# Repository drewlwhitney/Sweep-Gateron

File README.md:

[Head Repository](https://github.com/davidphilipbarr/Sweep)

# Sweep Gateron

<sub>Wireless Ferris Sweep with Gateron KS-33 switches and [Nyphy COAST Dawn](https://nuphy.com/collections/keycaps/products/coast-dawn-nsa?_pos=16&_fid=9b29c1ae1&_ss=c) keycaps</sub>

A modified Ferris Sweep for [Gateron KS-33 switches](https://www.gateron.co/products/gateron-low-profile-mechanical-switch-set) ([hotswap sockets](https://www.gateron.com/products/gateron-low-profile-switch-hot-swap-pcb-socket?VariantsId=10234) required).

## Variants
- [Basic](./Sweep-Gateron/) - MX spacing, based on the [Sweep High](https://github.com/davidphilipbarr/Sweep/tree/main/Sweep%20High).
- [JST](./Sweep-Gateron/jst/) - Same as the basic version, but the TRS jack is replaced with a 2-pin JST connector for the battery in wireless builds (and the reset button is moved). **Wireless only**.
- [JST-TRS](./Sweep-Gateron/jst-trs/) - Same as the basic version, but adds a 2-pin JST connector (for a battery) on top of the TRS jack. Can be used for wired *or* wireless builds.

All variants support a [switch plate](./Sweep-Gateron/switch-plate/) and [bottom plate](./Sweep-Gateron/bottom-plate/).

## Components
Unless otherwise stated, this Sweep uses the same components as the base Sweep.

- The JST connector for the JST version is from [typeractive](https://typeractive.xyz/products/battery-jack).

- This board *does not* support a tenting puck, but great alternatives are tenting kickstands (from [typeractive](https://typeractive.xyz/products/battery-jack))
 or MagSafe tenting stands (from [Keebio](https://keeb.io/products/magnetic-magsafe-tenting-stand-kit-for-split-keyboard-r2)).

## Gallery
### Front

### Back

## Notes
- If you edit this board, be aware that the schematic files are affected by [#75](https://github.com/davidphilipbarr/Sweep/issues/75). The PCB files are correct according to the software pinout, however, and will be manufactured correctly.

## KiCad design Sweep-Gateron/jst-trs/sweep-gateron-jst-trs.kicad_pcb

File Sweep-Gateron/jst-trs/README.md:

# Sweep Gateron (JST-TRS)
Adds a 2-pin JST connector in the same position as the TRS connector. This can be used for wired or wireless builds. The JST connector can be purchased [here](https://typeractive.xyz/products/battery-jack).

## Build Instructions
See the [Sweep High](https://github.com/davidphilipbarr/Sweep/tree/main/Sweep%20Bling%20MX) folder for PCB manufacturing instructions.

### Gerber Files
Can be found [here](./gerber_to_order/).

### Switch Plate and Bottom Plate
Can be found [here](../switch-plate/) and [here](../bottom-plate/), respectively.

## Added Footprints
- [2-pin JST Connector](https://app.ultralibrarian.com/details/fbd6f894-563c-11ea-8c00-0ad2c9526b44/JST/S2B-PH-K-S-LF-SN-?exports=42&open=exports)

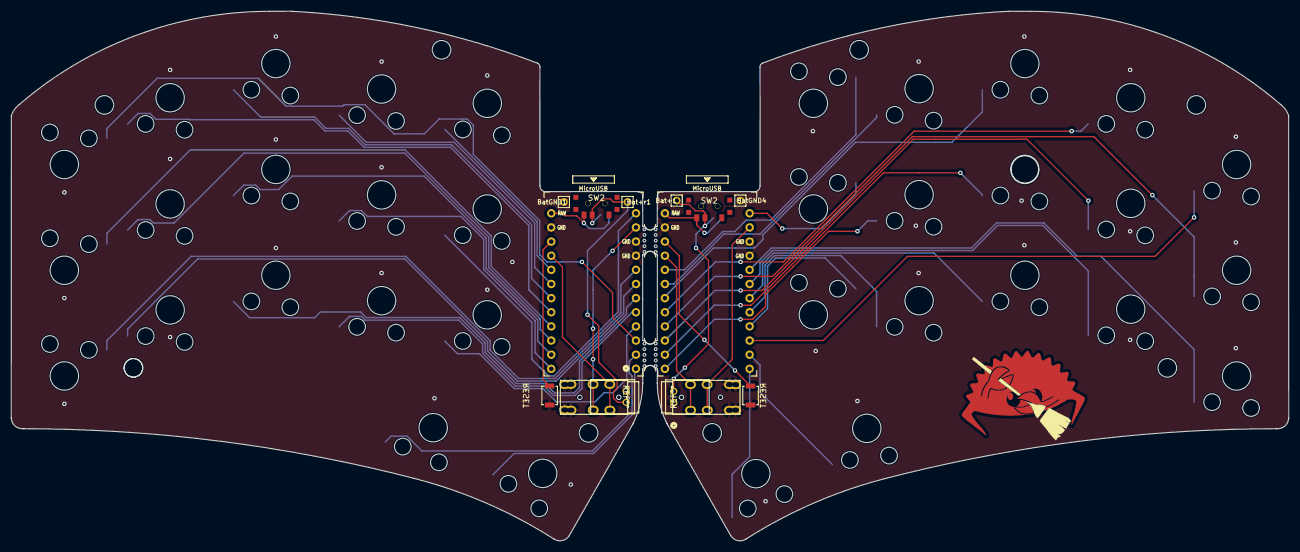
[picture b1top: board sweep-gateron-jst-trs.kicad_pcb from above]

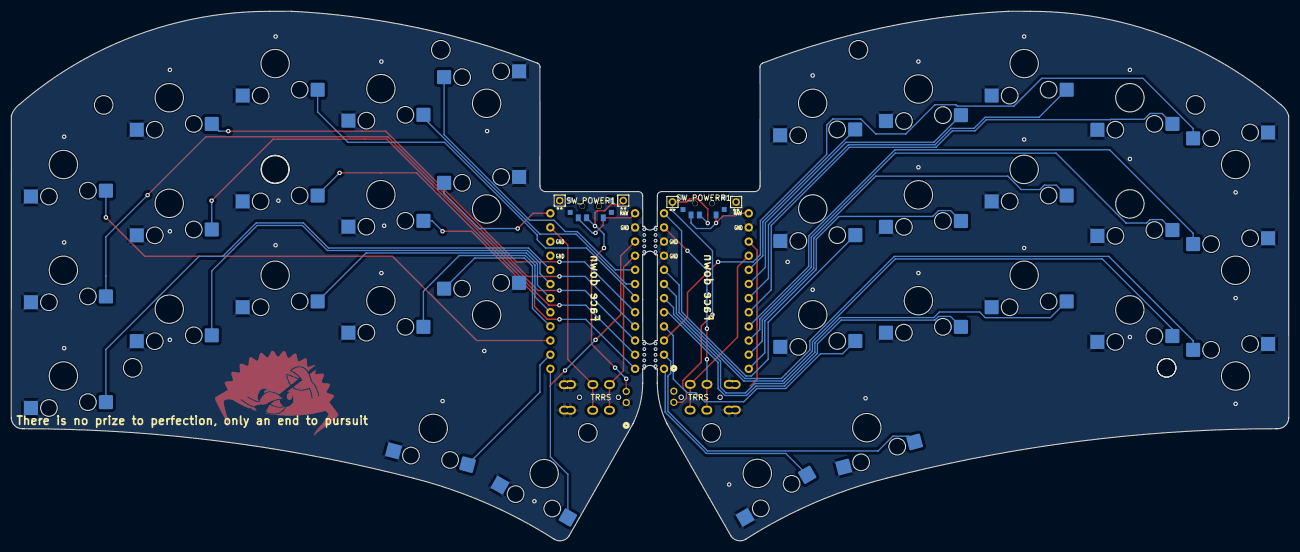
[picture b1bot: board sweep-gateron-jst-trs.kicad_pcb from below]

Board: 2 copper layers, 229.5 x 95.2 mm, 58 parts (40 on the bottom side), 43 nets.

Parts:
Bat+1: MountingHole_Pad; 1pin_conn
Bat+r1: MountingHole_Pad; 1pin_conn
BatGND1, BatGND4: MountingHole_Pad; 1pin_conn
J1, J2: AudioJack4dpb; TRRS-PJ-DPB2
Mounting 01, Mounting 01#2, Mounting 02, Mounting 02#2, Mounting 03, Mounting 03#2, Mounting 04, Mounting 04#2: MountingHole_3.35mm
RSW1, RSW2: SW_Push; SW_SPST_B3U-1000P
SW2, SW2#2: SW_SPDT; SPDT_C128955r
SW2#3, SW2_r1, SW3, SW3_r1, SW4, SW4_r1, SW5, SW5_r1, SW6, SW6_r1, SW7_r1, SW8, SW8_r1, SW9, SW9_r1, SW10, SW10_r1, SW11, SW11_r1, SW12, SW12_r1, SW13_r1, SW14, SW14_r1, SW15, SW15_r1, SW16, SW16_r1, SW17, SW18, SW20, SW20#2, SW21, SW21#2: SW_Push; Gateron-KS33-Hotswap-1U
SW_POWER1: SW_SPDT; SPDT_C128955
SW_POWERR1: SW_SPDT; SPDT_C128955
U1, U2: ProMicro-kbd; ProMicro_v3_min
mouse-bite-5mm-slot, mouse-bite-5mm-slot#2: VAL**; mouse-bite-5mm-slot-with-space-for-track

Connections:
BT+: Bat+1.1, SW2.2, SW_POWER1.2 (B)
BT+_r: Bat+r1.1, SW2#2.2, SW_POWERR1.2 (B)
Switch1: SW2#3.1, U1.10 (E6)
Switch1_r: SW2_r1.1, U2.10 (E6)
Switch2: SW3.1, U1.17 (F7)
Switch2_r: SW3_r1.1, U2.17 (F7)
Switch3: SW4.1, U1.18 (F6)
Switch3_r: SW4_r1.1, U2.18 (F6)
Switch4: SW5.1, U1.19 (F5)
Switch4_r: SW5_r1.1, U2.19 (F5)
Switch5: SW6.1, U1.20 (F4)
Switch5_r: SW6_r1.1, U2.20 (F4)
Switch6: SW8.1, U1.16 (B1)
Switch6_r: SW7_r1.1, U2.16 (B1)
Switch7: SW9.1, U1.15 (B3)
Switch7_r: SW8_r1.1, U2.15 (B3)
Switch8: SW10.1, U1.14 (B2)
Switch8_r: SW9_r1.1, U2.14 (B2)
Switch9: SW11.1, U1.13 (B6)
Switch9_r: SW10_r1.1, U2.13 (B6)
Switch10: SW12.1, U1.1 (TX)
Switch10_r: SW11_r1.1, U2.1 (TX)
Switch11: SW14.1, U1.5 (SDA)
Switch11_r: SW12_r1.1, U2.5 (SDA)
Switch12: SW15.1, U1.6 (SCL)
Switch12_r: SW13_r1.1, U2.6 (SCL)
Switch13: SW16.1, U1.7 (D4)
Switch13_r: SW14_r1.1, U2.7 (D4)
Switch14: SW17.1, U1.8 (C6)
Switch14_r: SW15_r1.1, U2.8 (C6)
Switch15: SW18.1, U1.9 (D7)
Switch15_r: SW16_r1.1, U2.9 (D7)
Switch16: SW20.1, U1.11 (B4)
Switch16_r: SW20#2.1, U2.11 (B4)
Switch17: SW21.1, U1.12 (B5)
Switch17_r: SW21#2.1, U2.12 (B5)
Switch18: J2.R1, U1.2 (RX)
Switch18_r: J1.R1, U2.2 (RX)
gnd: BatGND1.1, BatGND4.1, J1.S, J1.T, J2.S, J2.T, RSW1.1, RSW2.1, SW2#3.2, SW2_r1.2, SW3.2, SW3_r1.2, SW4.2, SW4_r1.2, SW5.2, SW5_r1.2, SW6.2, SW6_r1.2, SW7_r1.2, SW8.2, SW8_r1.2, SW9.2, SW9_r1.2, SW10.2, SW10_r1.2, SW11.2, SW11_r1.2, SW12.2, SW12_r1.2, SW13_r1.2, SW14.2, SW14_r1.2, SW15.2, SW15_r1.2, SW16.2, SW16_r1.2, SW17.2, SW18.2, SW20.2, SW20#2.2, SW21.2, SW21#2.2, U1.3 (GND), U1.4 (GND), U1.23 (GND), U2.3 (GND), U2.4 (GND), U2.23 (GND)
raw: SW2.3, SW2#2.3, SW_POWER1.3 (C), SW_POWERR1.3 (C), U1.24 (RAW), U2.24 (RAW)
reset: RSW1.2, U1.22 (RST)
reset_r: RSW2.2, U2.22 (RST)
vcc: J1.R2, J2.R2, U1.21 (VCC), U2.21 (VCC)

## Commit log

2025-11-30 Made a lot of progress routing the gateron pcb
2025-11-30 Routed the right side pcb
2025-11-30 Making sure we're up to date
2025-12-01 Had my friend look at the board, routing seems okay. Added some via stitches for better ground plane continuity
2025-12-01 Renamed some of the plate files. Just need to create the gerber files now
2025-12-02 Added a version that replaces the TRRS connector with a JST connector for wireless builds
2025-12-02 Added gerber files
2025-12-23 Fixed swapped pads and generated gerber files
2025-12-23 Built the board and updated the documentation
2025-12-23 Mirrored the documetation for the basic version in the JST version
2025-12-23 Changed the name of the Sweep Gateron folder to fix link issues in the docs
2025-12-23 Fixed more link issues
2025-12-23 Added the missing gerber files
2025-12-26 Added a JST version that also has a TRS jack so you can order one board for both wired and wireless builds
